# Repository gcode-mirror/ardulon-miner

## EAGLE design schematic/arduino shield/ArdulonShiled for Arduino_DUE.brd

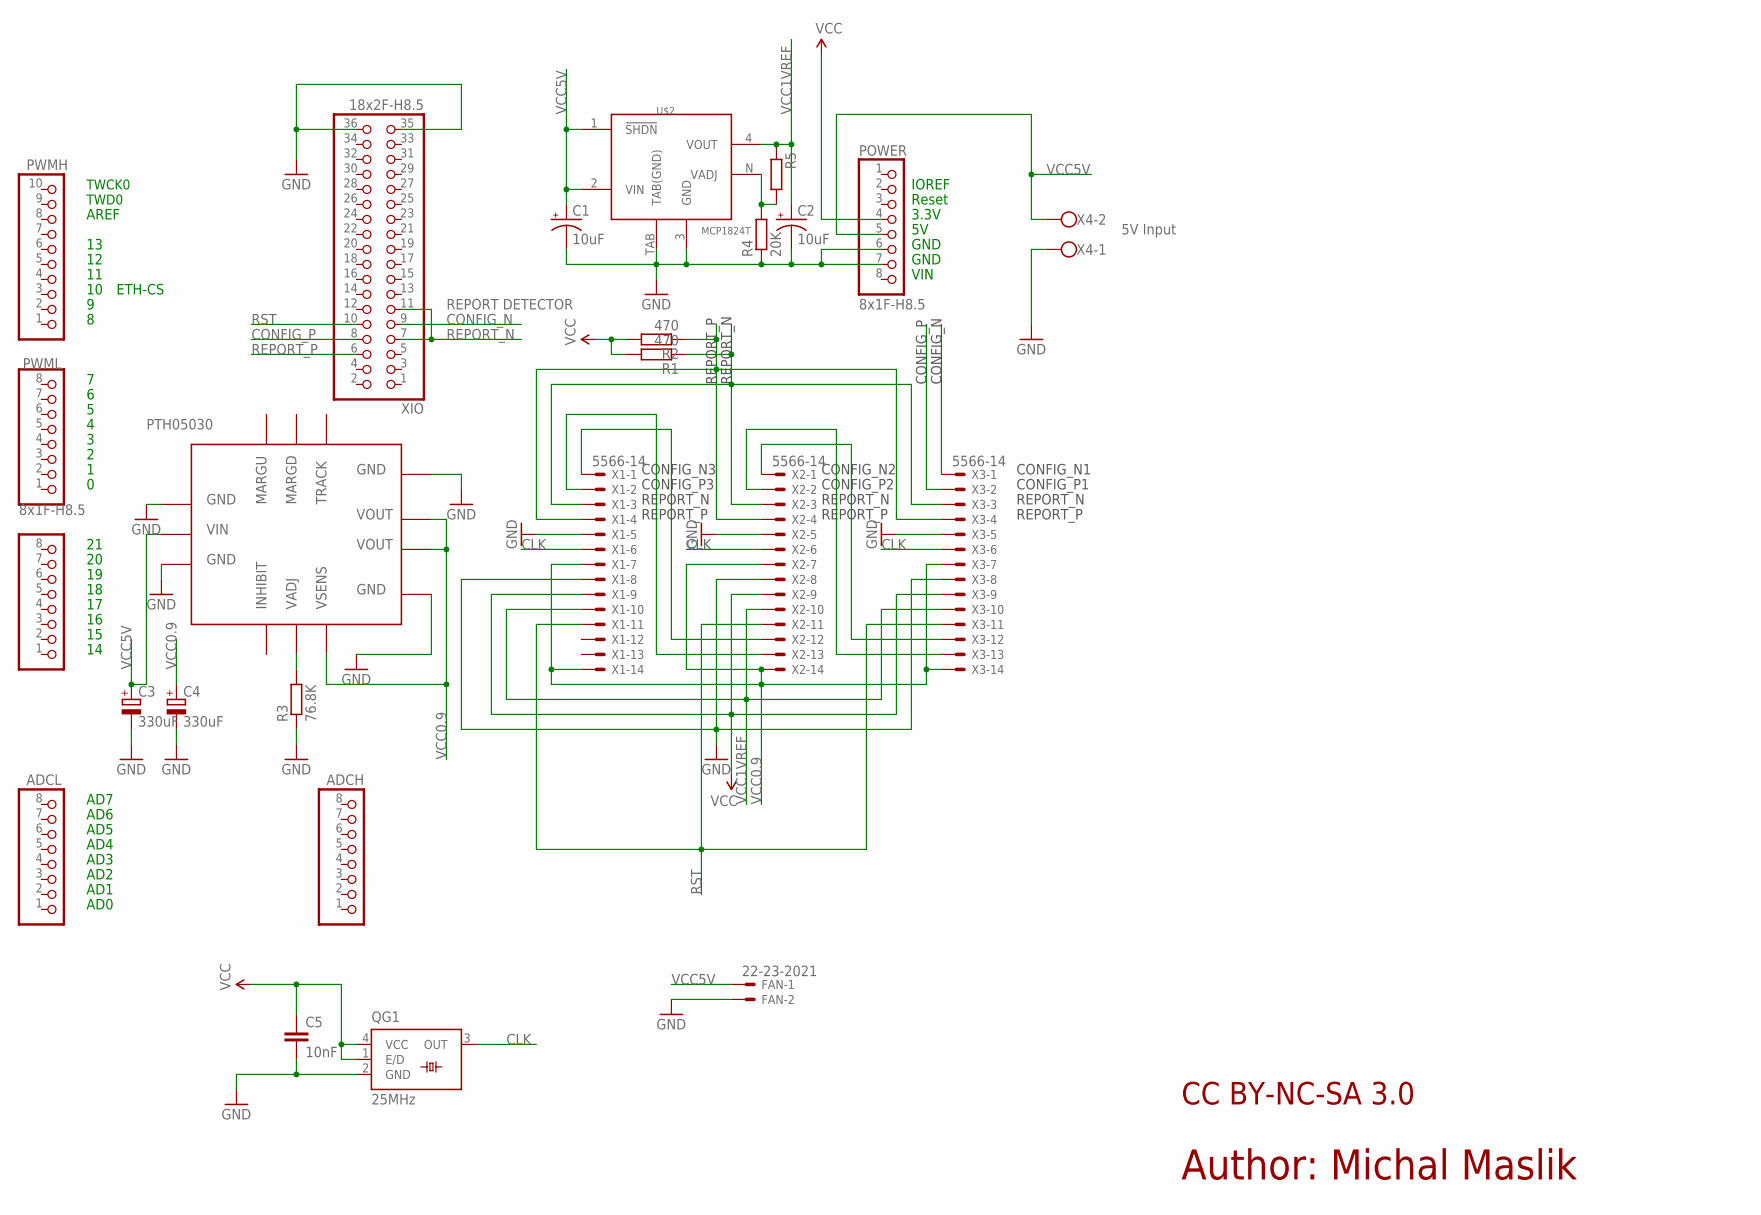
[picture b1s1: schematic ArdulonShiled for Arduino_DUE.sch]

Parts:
ADCH: 8x1F-H8.5; 1X08
ADCL: 8x1F-H8.5; 1X08
C1, C2: 10uF; EIA3528-KIT
C3, C4: 330uF; SMC_E
C5: 10nF; C0805
COMMUNICATION: 8x1F-H8.5; 1X08
FAN: 22-23-2021
POWER: 8x1F-H8.5; 1X08
PWMH: 10x1F-H8.5; 1X10
PWML: 8x1F-H8.5; 1X08
QG1: 25MHz; SM77H
R1, R2: 470; M0805
R3: 76.8K; M0805
R4: 20K; M0805
R5: R-EU_M0805; M0805
U$1: PTH05030
U$2: MCP1824T; SOT223-5
X1, X2, X3: 5566-14
X4: W237-102
XIO: 18x2F-H8.5; 2X18

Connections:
CLK: QG1.3 (OUT), X1.6, X2.6, X3.6
CONFIG_N: X3.1, XIO.9
CONFIG_P: X3.2, XIO.8
GND: C1.C (-), C2.C (-), C3.-, C4.-, C5.2, FAN.2, POWER.6, POWER.7, QG1.2 (GND), R3.1, R4.1, U$1.1, U$1.3, U$1.7, U$1.10, U$2.3 (GND), U$2.TAB (TAB(GND)), X1.5, X1.8, X2.5, X2.8, X3.5, X3.8, X4.1, XIO.35, XIO.36
unnamed: R4.2, R5.2, U$2.N (VADJ)
unnamed: X2.1, X3.12
unnamed: R3.2, U$1.5
unnamed: X2.2, X3.13
unnamed: X1.1, X2.12
unnamed: X1.2, X2.13
REPORT_N: R1.1, X1.3, X2.3, X3.3, XIO.7, XIO.11
REPORT_P: R2.1, X1.4, X2.4, X3.4, XIO.6
RST: X1.11, X2.11, X3.11, XIO.10
VCC: C5.1, POWER.4, QG1.1 (E/D), QG1.4 (VCC), R1.2, R2.2, X1.9, X2.9, X3.9
VCC0.9: C4.+, U$1.6, U$1.8, U$1.9, X1.7, X1.14, X2.7, X2.14, X3.7, X3.14
VCC1REF: C2.A (+), R5.1, U$2.4 (VOUT), X1.10, X2.10, X3.10
VCC5V: C1.A (+), C3.+, FAN.1, POWER.5, U$1.2, U$2.1 (!SHDN), U$2.2 (VIN), X4.2

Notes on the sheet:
IOREF
TWCK0
TWD0
AD1
AD2
AD3
AD4
AD5
AD6
AD0
AREF
AD7
ETH-CS
3.3V
GND
VIN
Reset
REPORT_P
REPORT_N
CONFIG_P
CONFIG_N
VCC1VREF
VCC0.9
5V Input
VCC5V
RST
CONFIG_N1
CONFIG_P1
CONFIG_N2
CONFIG_P2
CONFIG_P3
CONFIG_N3
CLK
Author: Michal Maslik
REPORT DETECTOR
CC BY-NC-SA 3.0

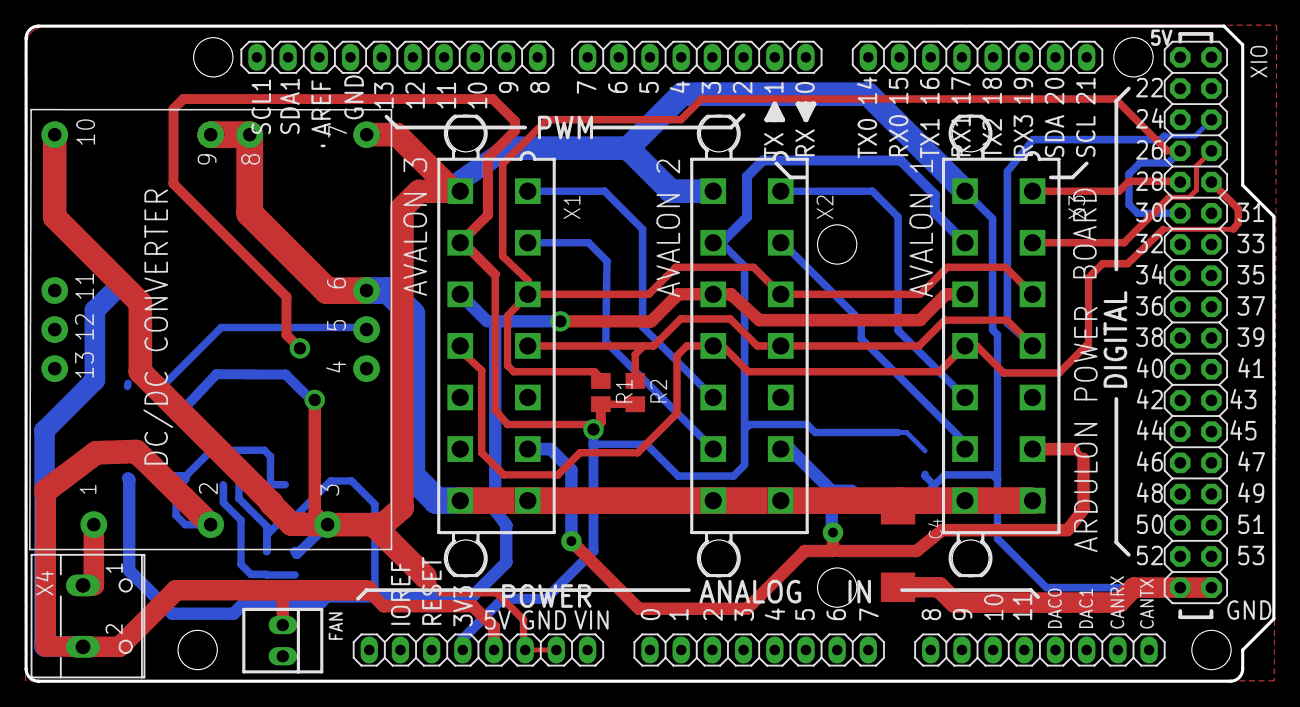
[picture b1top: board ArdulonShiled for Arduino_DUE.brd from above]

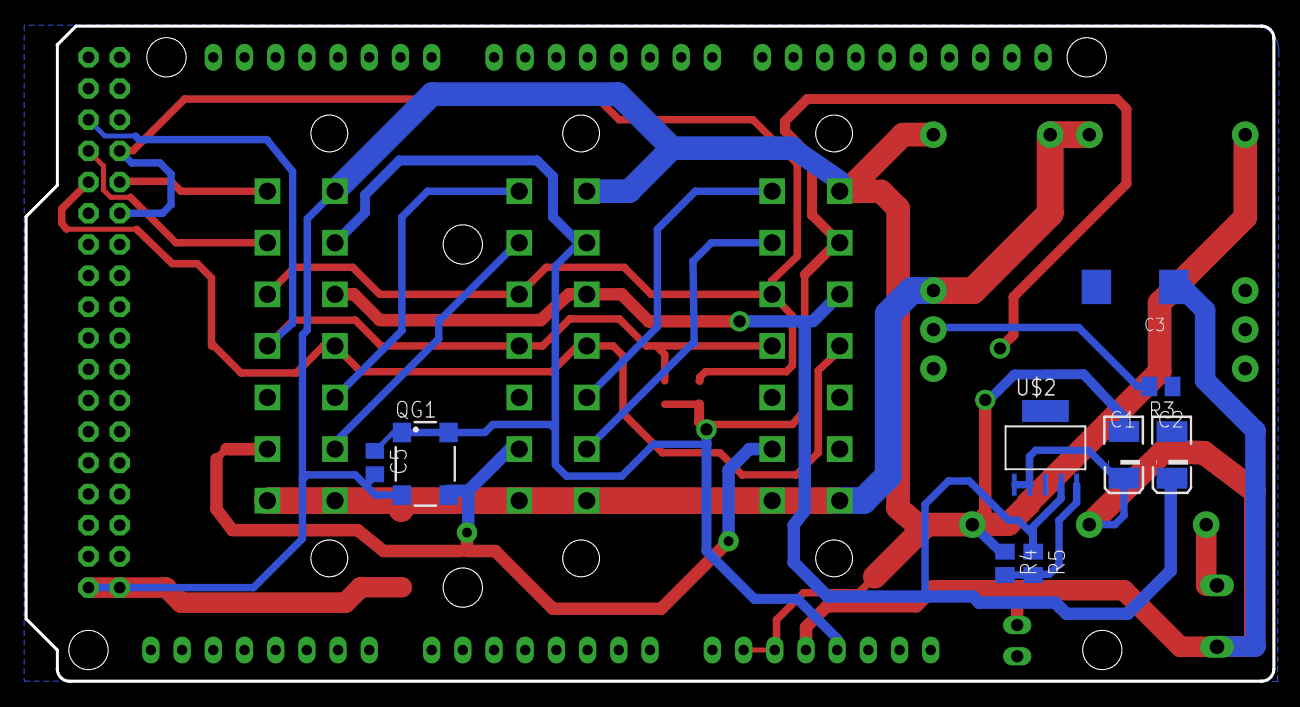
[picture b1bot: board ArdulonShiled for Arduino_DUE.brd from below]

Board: 4 copper layers, 101.6 x 53.3 mm, 25 parts (9 on the bottom side), 17 nets.

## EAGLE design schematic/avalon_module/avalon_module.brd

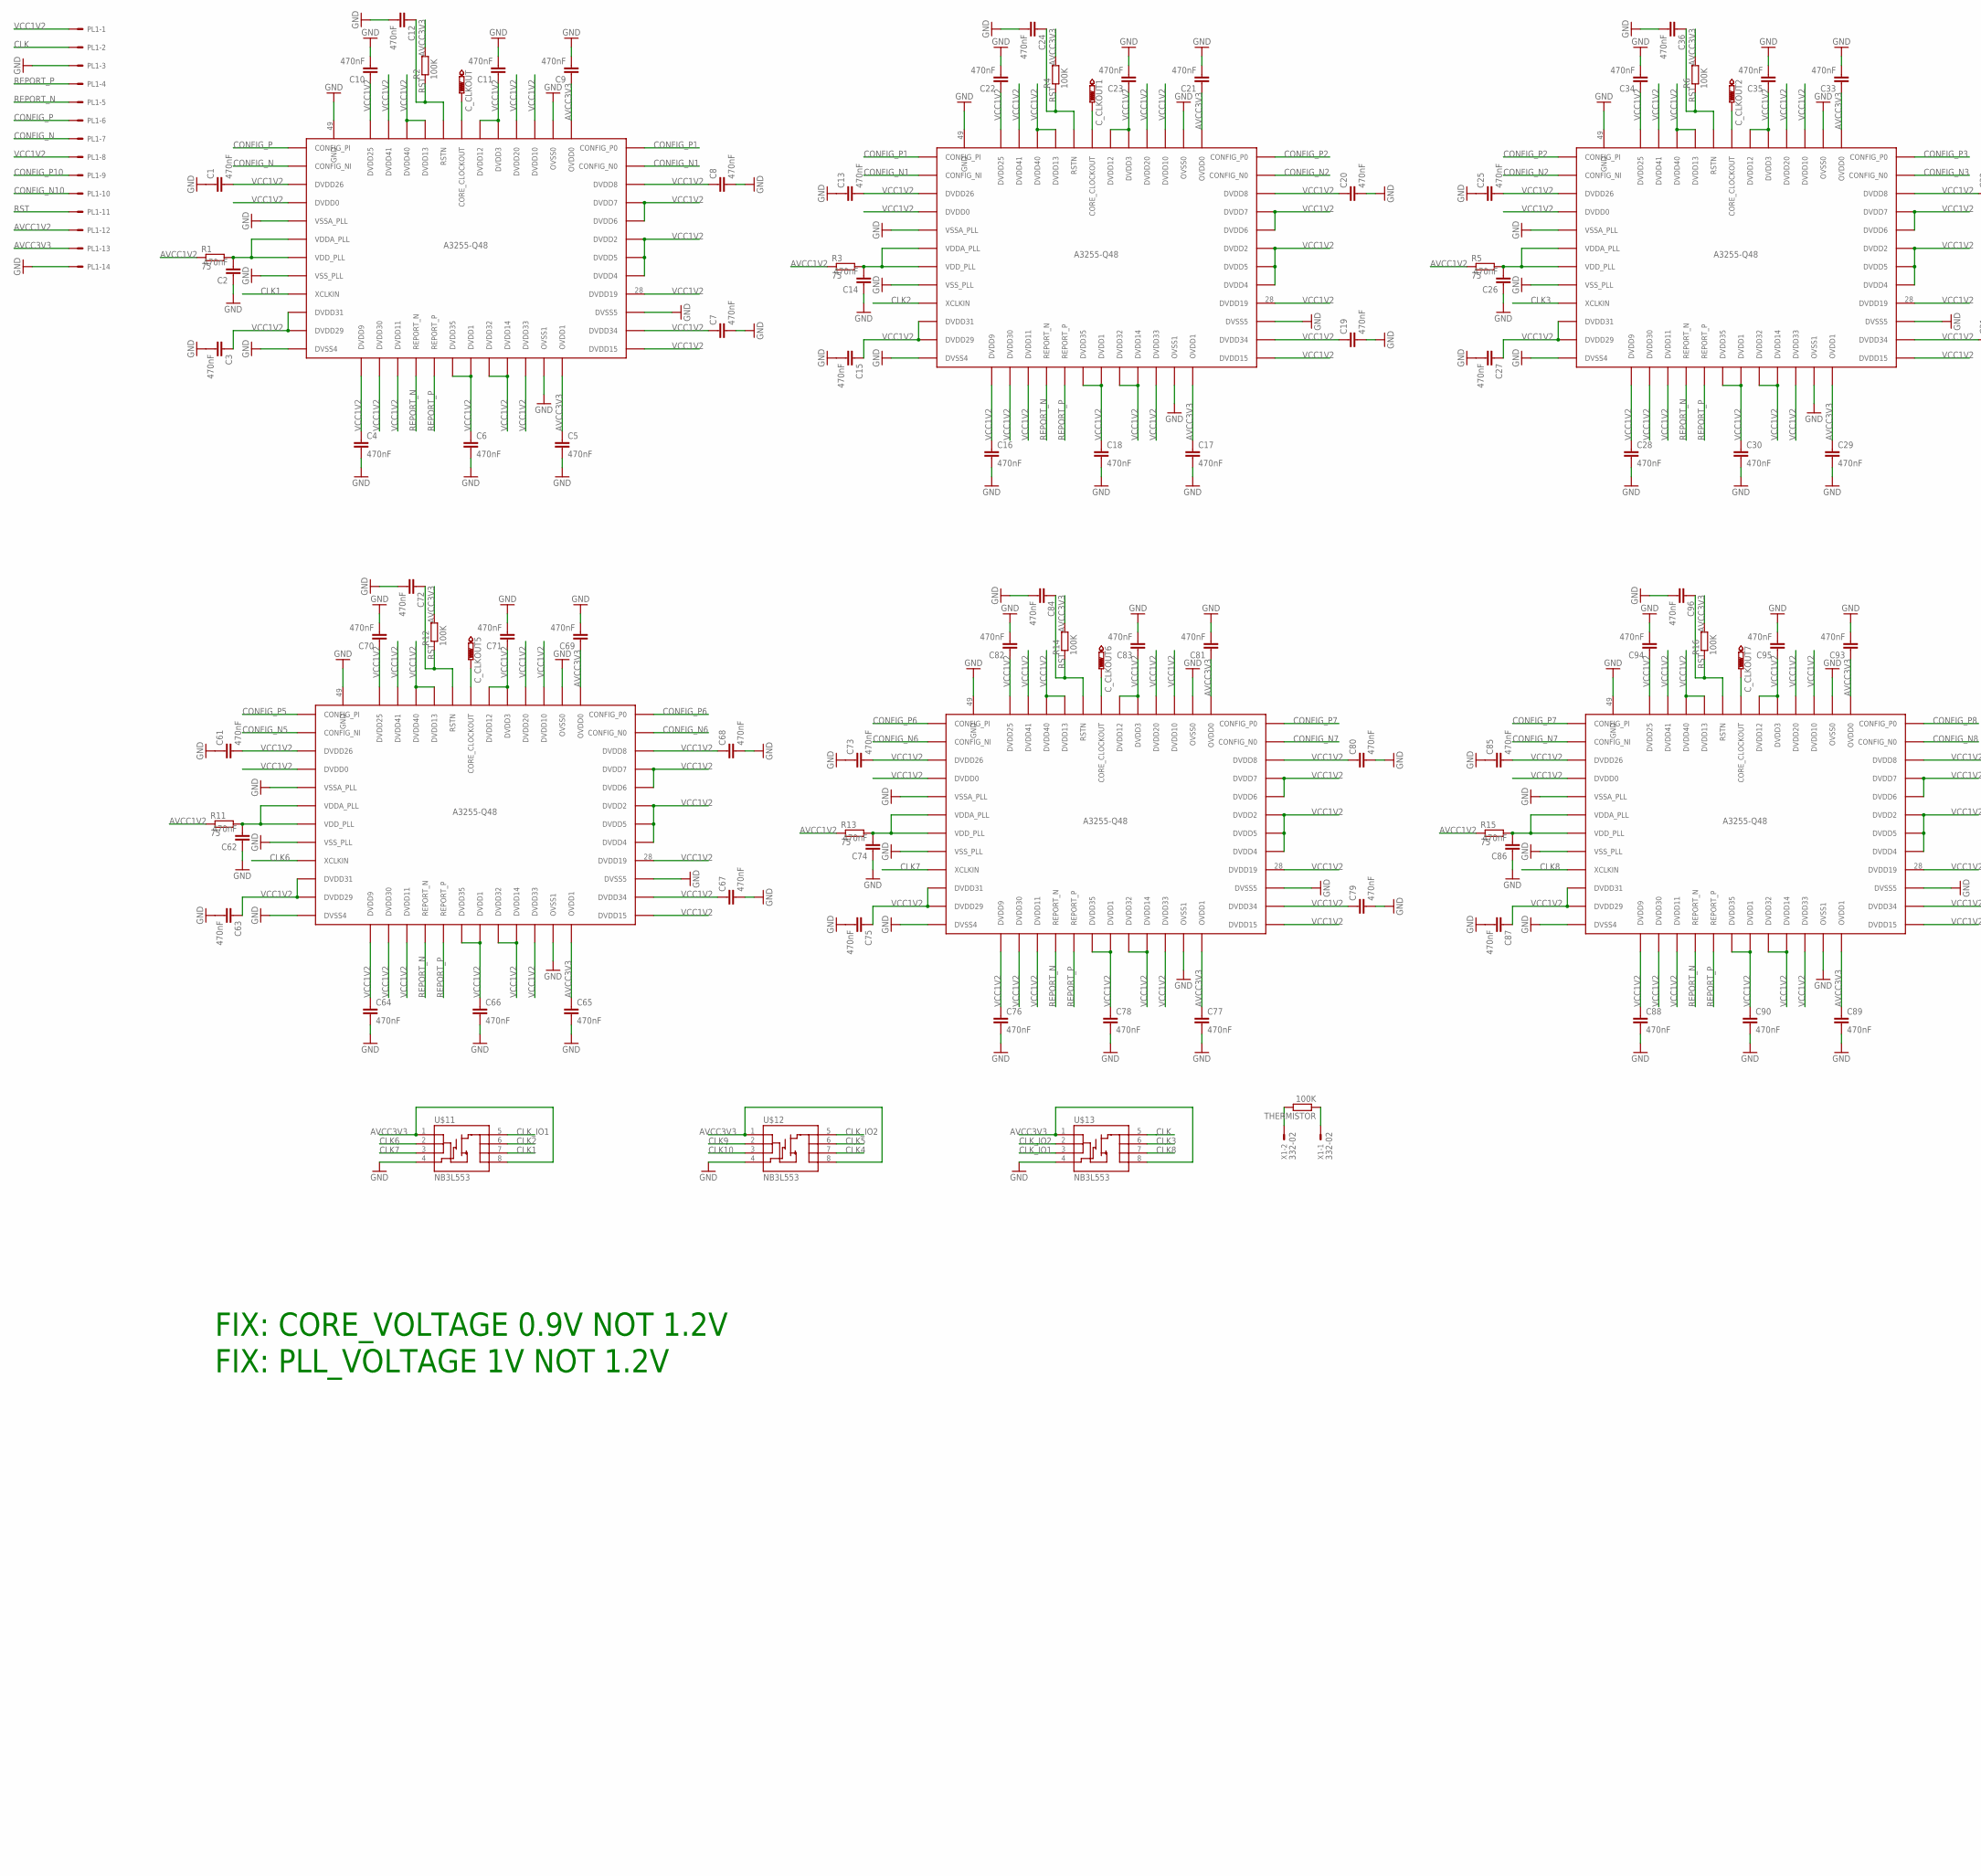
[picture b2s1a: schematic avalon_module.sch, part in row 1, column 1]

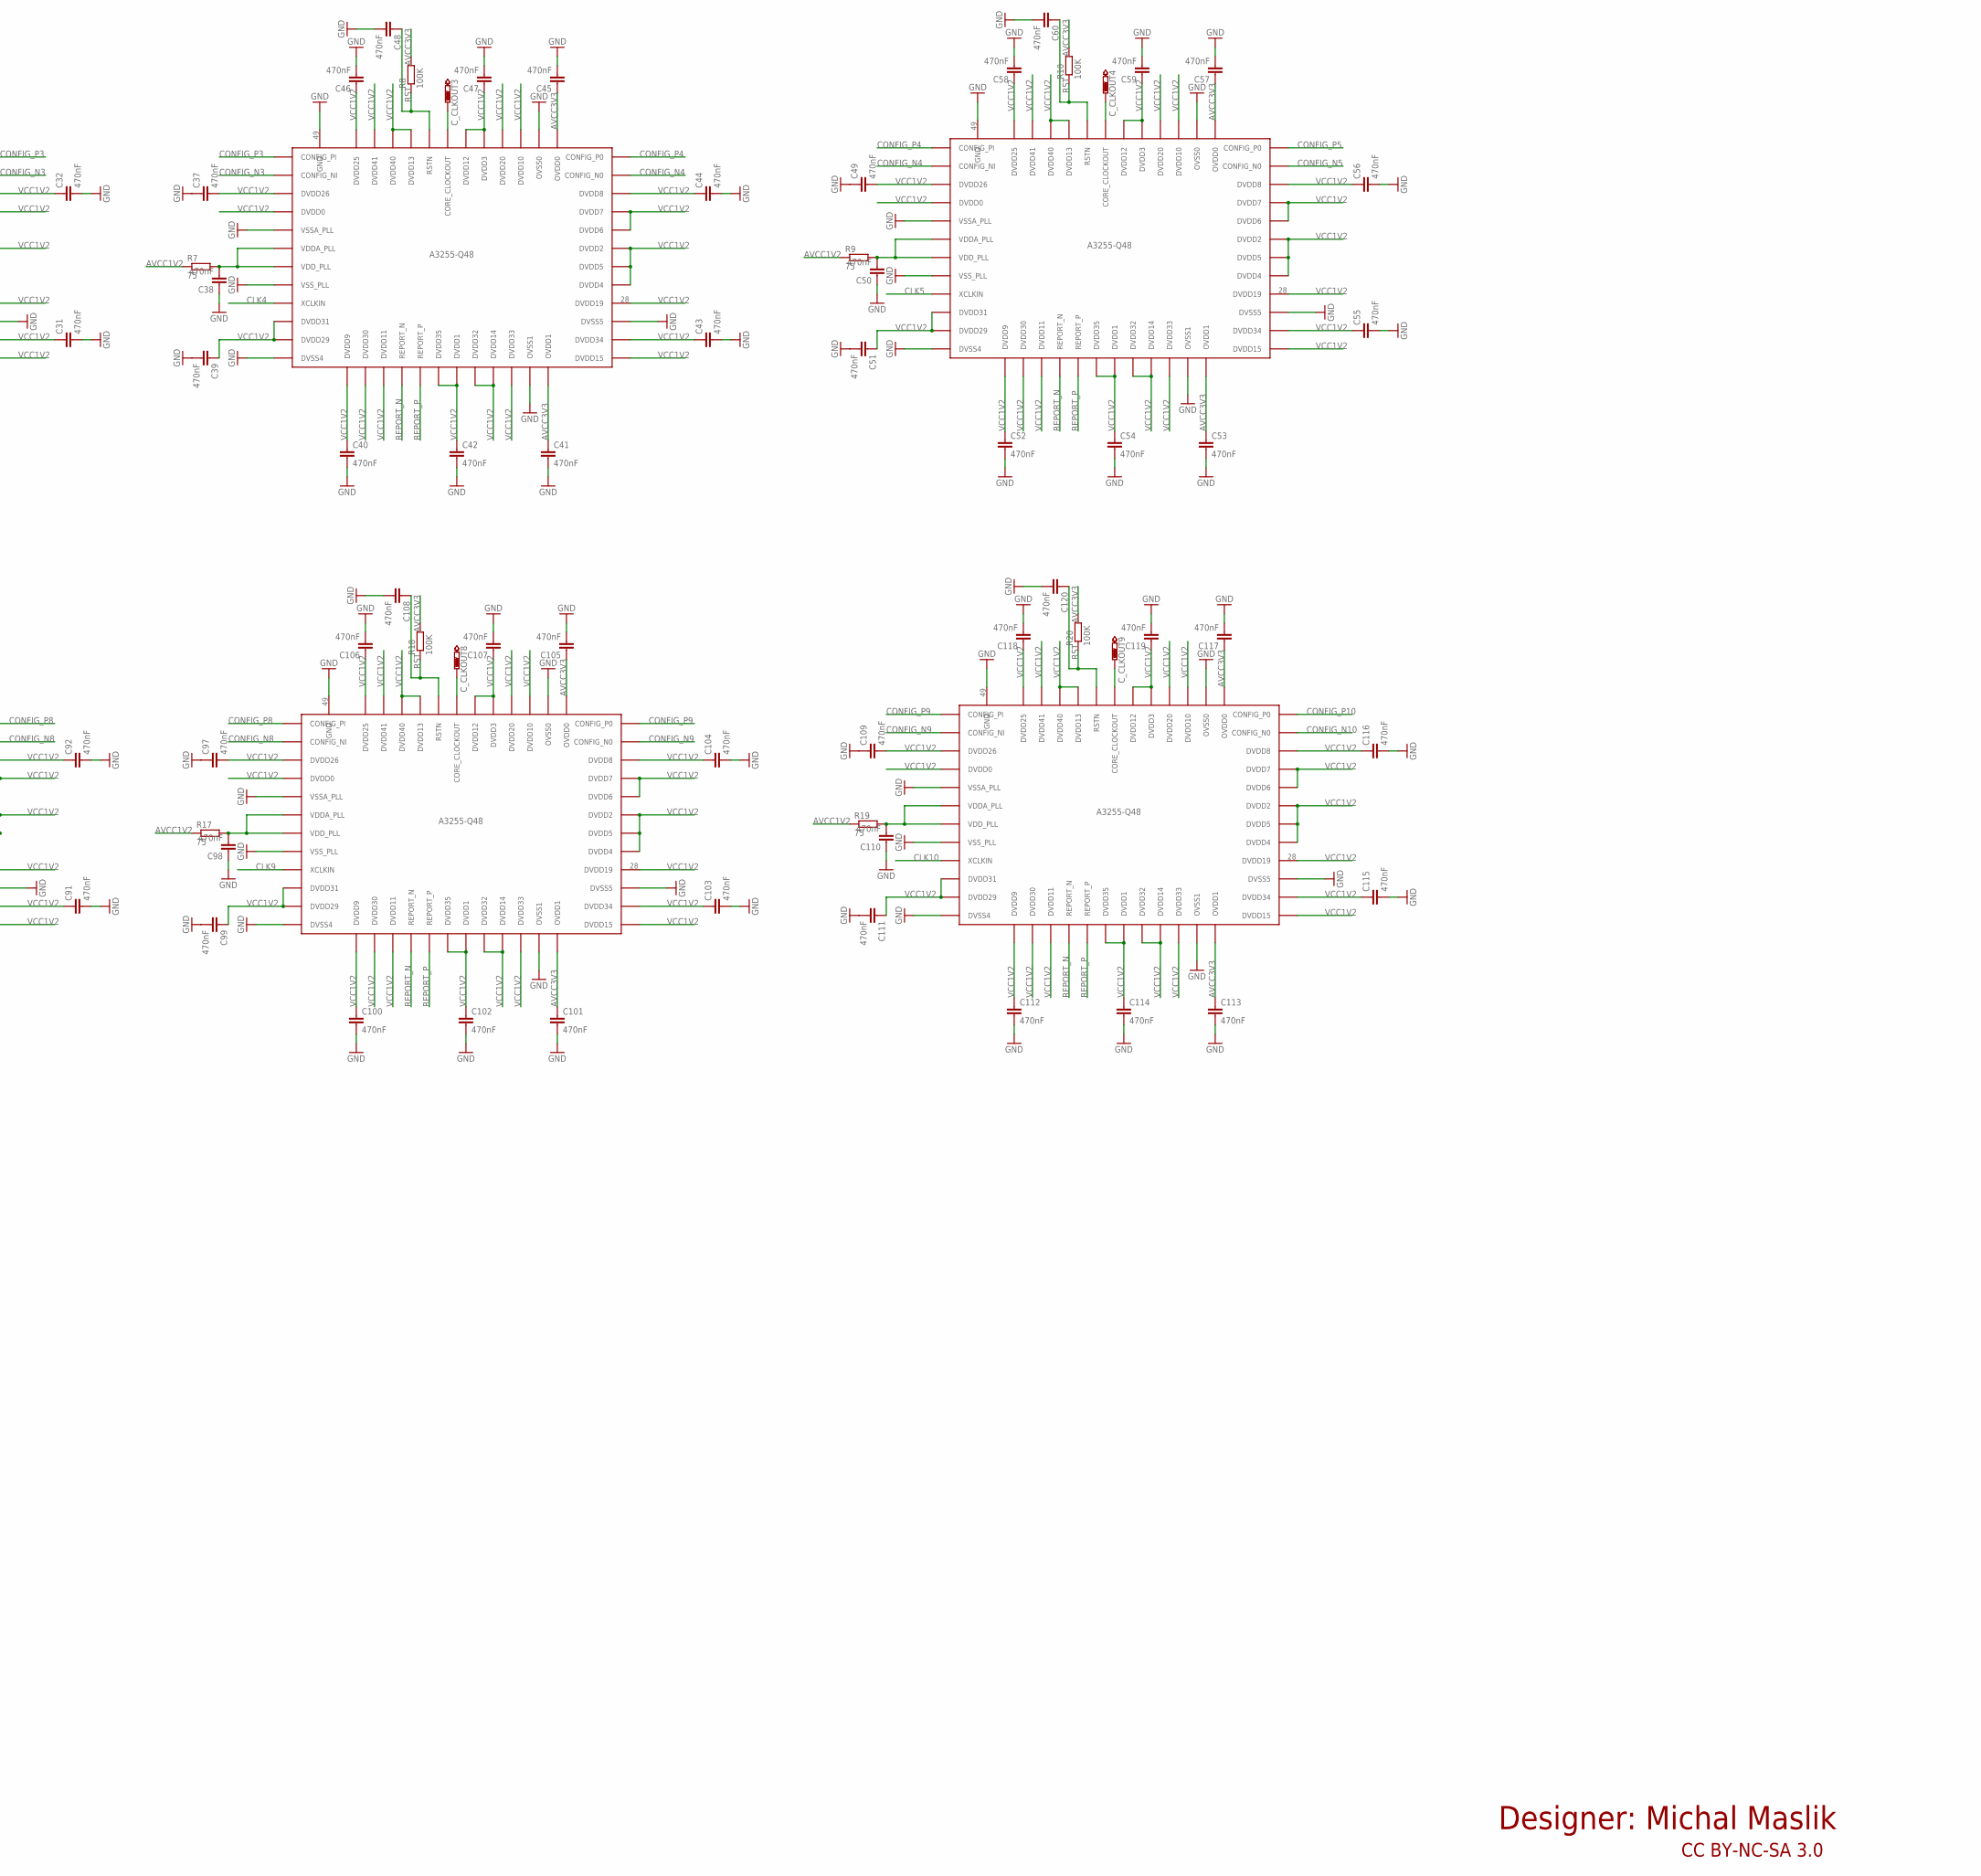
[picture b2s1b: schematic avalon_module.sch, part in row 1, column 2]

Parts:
C1, C2, C3, C4, C5, C6, C7, C8, C9, C10, C11, C12, C13, C14, C15, C16, C17, C18, C19, C20, C21, C22, C23, C24, C25, C26, C27, C28, C29, C30, C31, C32, C33, C34, C35, C36, C37, C38, C39, C40, C41, C42, C43, C44, C45, C46, C47, C48, C49, C50, C51, C52, C53, C54, C55, C56, C57, C58, C59, C60, C61, C62, C63, C64, C65, C66, C67, C68, C69, C70, C71, C72, C73, C74, C75, C76, C77, C78, C79, C80, C81, C82, C83, C84, C85, C86, C87, C88, C89, C90, C91, C92, C93, C94, C95, C96, C97, C98, C99, C100, C101, C102, C103, C104, C105, C106, C107, C108, C109, C110, C111, C112, C113, C114, C115, C116, C117, C118, C119, C120: 470nF; C0603K
C_CLKOUT, C_CLKOUT1, C_CLKOUT2, C_CLKOUT3, C_CLKOUT4, C_CLKOUT5, C_CLKOUT6, C_CLKOUT7, C_CLKOUT8, C_CLKOUT9: PTR1TP07R; TP07R
PL1: 555X-14H; 5569-14
R1, R3, R5, R7, R9, R11, R13, R15, R17, R19: 75; R0603
R2, R4, R6, R8, R10, R12, R14, R16, R18, R20: 100K; R0603
THERMISTOR: 100K; R0603
U$1, U$2, U$3, U$4, U$5, U$6, U$7, U$8, U$9, U$10: A3255Q48
U$11, U$12, U$13: NB3L553; SO08
X1: 332-02

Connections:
$1: C14.2, R3.2, U$2.6 (VDDA_PLL), U$2.7 (VDD_PLL)
$2: C26.2, R5.2, U$3.6 (VDDA_PLL), U$3.7 (VDD_PLL)
$3: C2.2, R1.2, U$1.6 (VDDA_PLL), U$1.7 (VDD_PLL)
$4: C38.2, R7.2, U$4.6 (VDDA_PLL), U$4.7 (VDD_PLL)
$5: C50.2, R9.2, U$5.6 (VDDA_PLL), U$5.7 (VDD_PLL)
$6: C62.2, R11.2, U$6.6 (VDDA_PLL), U$6.7 (VDD_PLL)
$7: C74.2, R13.2, U$7.6 (VDDA_PLL), U$7.7 (VDD_PLL)
$8: C86.2, R15.2, U$8.6 (VDDA_PLL), U$8.7 (VDD_PLL)
$9: C98.2, R17.2, U$9.6 (VDDA_PLL), U$9.7 (VDD_PLL)
$10: C110.2, R19.2, U$10.6 (VDDA_PLL), U$10.7 (VDD_PLL)
AVCC1V2: PL1.12, R1.1, R3.1, R5.1, R7.1, R9.1, R11.1, R13.1, R15.1, R17.1, R19.1
AVCC3V3: C5.1, C9.1, C17.1, C21.1, C29.1, C33.1, C41.1, C45.1, C53.1, C57.1, C65.1, C69.1, C77.1, C81.1, C89.1, C93.1, C101.1, C105.1, C113.1, C117.1, PL1.13, R2.2, R4.2, R6.2, R8.2, R10.2, R12.2, R14.2, R16.2, R18.2, R20.2, U$1.24 (OVDD1), U$1.37 (OVDD0), U$2.24 (OVDD1), U$2.37 (OVDD0), U$3.24 (OVDD1), U$3.37 (OVDD0), U$4.24 (OVDD1), U$4.37 (OVDD0), U$5.24 (OVDD1), U$5.37 (OVDD0), U$6.24 (OVDD1), U$6.37 (OVDD0), U$7.24 (OVDD1), U$7.37 (OVDD0), U$8.24 (OVDD1), U$8.37 (OVDD0), U$9.24 (OVDD1), U$9.37 (OVDD0), U$10.24 (OVDD1), U$10.37 (OVDD0), U$11.1 (S), U$11.8 (D), U$12.1 (S), U$12.8 (D), U$13.1 (S), U$13.8 (D)
CLK: PL1.2, U$13.5 (D)
CLK1: U$1.9 (XCLKIN), U$11.7 (D)
CLK2: U$2.9 (XCLKIN), U$11.6 (D)
CLK3: U$3.9 (XCLKIN), U$13.6 (D)
CLK4: U$4.9 (XCLKIN), U$12.7 (D)
CLK5: U$5.9 (XCLKIN), U$12.6 (D)
CLK6: U$6.9 (XCLKIN), U$11.2 (S)
CLK7: U$7.9 (XCLKIN), U$11.3 (S)
CLK8: U$8.9 (XCLKIN), U$13.7 (D)
CLK9: U$9.9 (XCLKIN), U$12.2 (S)
CLK10: U$10.9 (XCLKIN), U$12.3 (S)
CLK_IO1: U$11.5 (D), U$13.3 (S)
CLK_IO2: U$12.5 (D), U$13.2 (S)
CONFIG_N: PL1.7, U$1.2 (CONFIG_NI)
CONFIG_N1: U$1.35 (CONFIG_N0), U$2.2 (CONFIG_NI)
CONFIG_N2: U$2.35 (CONFIG_N0), U$3.2 (CONFIG_NI)
CONFIG_N3: U$3.35 (CONFIG_N0), U$4.2 (CONFIG_NI)
CONFIG_N4: U$4.35 (CONFIG_N0), U$5.2 (CONFIG_NI)
CONFIG_N5: U$5.35 (CONFIG_N0), U$6.2 (CONFIG_NI)
CONFIG_N6: U$6.35 (CONFIG_N0), U$7.2 (CONFIG_NI)
CONFIG_N7: U$7.35 (CONFIG_N0), U$8.2 (CONFIG_NI)
CONFIG_N8: U$8.35 (CONFIG_N0), U$9.2 (CONFIG_NI)
CONFIG_N9: U$9.35 (CONFIG_N0), U$10.2 (CONFIG_NI)
CONFIG_N10: PL1.10, U$10.35 (CONFIG_N0)
CONFIG_P: PL1.6, U$1.1 (CONFIG_PI)
CONFIG_P1: U$1.36 (CONFIG_P0), U$2.1 (CONFIG_PI)
CONFIG_P2: U$2.36 (CONFIG_P0), U$3.1 (CONFIG_PI)
CONFIG_P3: U$3.36 (CONFIG_P0), U$4.1 (CONFIG_PI)
CONFIG_P4: U$4.36 (CONFIG_P0), U$5.1 (CONFIG_PI)
CONFIG_P5: U$5.36 (CONFIG_P0), U$6.1 (CONFIG_PI)
CONFIG_P6: U$6.36 (CONFIG_P0), U$7.1 (CONFIG_PI)
CONFIG_P7: U$7.36 (CONFIG_P0), U$8.1 (CONFIG_PI)
CONFIG_P8: U$8.36 (CONFIG_P0), U$9.1 (CONFIG_PI)
CONFIG_P9: U$9.36 (CONFIG_P0), U$10.1 (CONFIG_PI)
CONFIG_P10: PL1.9, U$10.36 (CONFIG_P0)
GND: C1.1, C2.1, C3.2, C4.2, C5.2, C6.2, C7.2, C8.2, C9.2, C10.2, C11.2, C12.2, C13.1, C14.1, C15.2, C16.2, C17.2, C18.2, C19.2, C20.2, C21.2, C22.2, C23.2, C24.2, C25.1, C26.1, C27.2, C28.2, C29.2, C30.2, C31.2, C32.2, C33.2, C34.2, C35.2, C36.2, C37.1, C38.1, C39.2, C40.2, C41.2, C42.2, C43.2, C44.2, C45.2, C46.2, C47.2, C48.2, C49.1, C50.1, C51.2, C52.2, C53.2, C54.2, C55.2, C56.2, C57.2, C58.2, C59.2, C60.2, C61.1, C62.1, C63.2, C64.2, C65.2, C66.2, C67.2, C68.2, C69.2, C70.2, C71.2, C72.2, C73.1, C74.1, C75.2, C76.2, C77.2, C78.2, C79.2, C80.2, C81.2, C82.2, C83.2, C84.2, C85.1, C86.1, C87.2, C88.2, C89.2, C90.2, C91.2, C92.2, C93.2, C94.2, C95.2, C96.2, C97.1, C98.1, C99.2, C100.2, C101.2, C102.2, C103.2, C104.2, C105.2, C106.2, C107.2, C108.2, C109.1, C110.1, C111.2, C112.2, C113.2, C114.2, C115.2, C116.2, C117.2, C118.2, C119.2, C120.2, PL1.3, PL1.14, U$1.5 (VSSA_PLL), U$1.8 (VSS_PLL), U$1.12 (DVSS4), U$1.23 (OVSS1), U$1.27 (DVSS5), U$1.38 (OVSS0), U$1.49 (GND), U$2.5 (VSSA_PLL), U$2.8 (VSS_PLL), U$2.12 (DVSS4), U$2.23 (OVSS1), U$2.27 (DVSS5), U$2.38 (OVSS0), U$2.49 (GND), U$3.5 (VSSA_PLL), U$3.8 (VSS_PLL), U$3.12 (DVSS4), U$3.23 (OVSS1), U$3.27 (DVSS5), U$3.38 (OVSS0), U$3.49 (GND), U$4.5 (VSSA_PLL), U$4.8 (VSS_PLL), U$4.12 (DVSS4), U$4.23 (OVSS1), U$4.27 (DVSS5), U$4.38 (OVSS0), U$4.49 (GND), U$5.5 (VSSA_PLL), U$5.8 (VSS_PLL), U$5.12 (DVSS4), U$5.23 (OVSS1), U$5.27 (DVSS5), U$5.38 (OVSS0), U$5.49 (GND), U$6.5 (VSSA_PLL), U$6.8 (VSS_PLL), U$6.12 (DVSS4), U$6.23 (OVSS1), U$6.27 (DVSS5), U$6.38 (OVSS0), U$6.49 (GND), U$7.5 (VSSA_PLL), U$7.8 (VSS_PLL), U$7.12 (DVSS4), U$7.23 (OVSS1), U$7.27 (DVSS5), U$7.38 (OVSS0), U$7.49 (GND), U$8.5 (VSSA_PLL), U$8.8 (VSS_PLL), U$8.12 (DVSS4), U$8.23 (OVSS1), U$8.27 (DVSS5), U$8.38 (OVSS0), U$8.49 (GND), U$9.5 (VSSA_PLL), U$9.8 (VSS_PLL), U$9.12 (DVSS4), U$9.23 (OVSS1), U$9.27 (DVSS5), U$9.38 (OVSS0), U$9.49 (GND), U$10.5 (VSSA_PLL), U$10.8 (VSS_PLL), U$10.12 (DVSS4), U$10.23 (OVSS1), U$10.27 (DVSS5), U$10.38 (OVSS0), U$10.49 (GND), U$11.4 (G), U$12.4 (G), U$13.4 (G)
unnamed: C_CLKOUT.TP, U$1.43 (CORE_CLOCKOUT)
unnamed: C_CLKOUT5.TP, U$6.43 (CORE_CLOCKOUT)
unnamed: C_CLKOUT1.TP, U$2.43 (CORE_CLOCKOUT)
unnamed: C_CLKOUT2.TP, U$3.43 (CORE_CLOCKOUT)
unnamed: C_CLKOUT3.TP, U$4.43 (CORE_CLOCKOUT)
unnamed: C_CLKOUT4.TP, U$5.43 (CORE_CLOCKOUT)
unnamed: C_CLKOUT9.TP, U$10.43 (CORE_CLOCKOUT)
unnamed: C_CLKOUT8.TP, U$9.43 (CORE_CLOCKOUT)
unnamed: C_CLKOUT7.TP, U$8.43 (CORE_CLOCKOUT)
unnamed: C_CLKOUT6.TP, U$7.43 (CORE_CLOCKOUT)
unnamed: THERMISTOR.2, X1.2
unnamed: THERMISTOR.1, X1.1
REPORT_N: PL1.5, U$1.16 (REPORT_N), U$2.16 (REPORT_N), U$3.16 (REPORT_N), U$4.16 (REPORT_N), U$5.16 (REPORT_N), U$6.16 (REPORT_N), U$7.16 (REPORT_N), U$8.16 (REPORT_N), U$9.16 (REPORT_N), U$10.16 (REPORT_N)
REPORT_P: PL1.4, U$1.17 (REPORT_P), U$2.17 (REPORT_P), U$3.17 (REPORT_P), U$4.17 (REPORT_P), U$5.17 (REPORT_P), U$6.17 (REPORT_P), U$7.17 (REPORT_P), U$8.17 (REPORT_P), U$9.17 (REPORT_P), U$10.17 (REPORT_P)
RST: C12.1, C24.1, C36.1, C48.1, C60.1, C72.1, C84.1, C96.1, C108.1, C120.1, PL1.11, R2.1, R4.1, R6.1, R8.1, R10.1, R12.1, R14.1, R16.1, R18.1, R20.1, U$1.44 (RSTN), U$2.44 (RSTN), U$3.44 (RSTN), U$4.44 (RSTN), U$5.44 (RSTN), U$6.44 (RSTN), U$7.44 (RSTN), U$8.44 (RSTN), U$9.44 (RSTN), U$10.44 (RSTN)
VCC1V2: C1.2, C3.1, C4.1, C6.1, C7.1, C8.1, C10.1, C11.1, C13.2, C15.1, C16.1, C18.1, C19.1, C20.1, C22.1, C23.1, C25.2, C27.1, C28.1, C30.1, C31.1, C32.1, C34.1, C35.1, C37.2, C39.1, C40.1, C42.1, C43.1, C44.1, C46.1, C47.1, C49.2, C51.1, C52.1, C54.1, C55.1, C56.1, C58.1, C59.1, C61.2, C63.1, C64.1, C66.1, C67.1, C68.1, C70.1, C71.1, C73.2, C75.1, C76.1, C78.1, C79.1, C80.1, C82.1, C83.1, C85.2, C87.1, C88.1, C90.1, C91.1, C92.1, C94.1, C95.1, C97.2, C99.1, C100.1, C102.1, C103.1, C104.1, C106.1, C107.1, C109.2, C111.1, C112.1, C114.1, C115.1, C116.1, C118.1, C119.1, PL1.1, PL1.8, U$1.3 (DVDD26), U$1.4 (DVDD0), U$1.10 (DVDD31), U$1.11 (DVDD29), U$1.13 (DVDD9), U$1.14 (DVDD30), U$1.15 (DVDD11), U$1.18 (DVDD35), U$1.19 (DVDD1), U$1.20 (DVDD32), U$1.21 (DVDD14), U$1.22 (DVDD33), U$1.25 (DVDD15), U$1.26 (DVDD34), U$1.28 (DVDD19), U$1.29 (DVDD4), U$1.30 (DVDD5), U$1.31 (DVDD2), U$1.32 (DVDD6), U$1.33 (DVDD7), U$1.34 (DVDD8), U$1.39 (DVDD10), U$1.40 (DVDD20), U$1.41 (DVDD3), U$1.42 (DVDD12), U$1.45 (DVDD13), U$1.46 (DVDD40), U$1.47 (DVDD41), U$1.48 (DVDD25), U$2.3 (DVDD26), U$2.4 (DVDD0), U$2.10 (DVDD31), U$2.11 (DVDD29), U$2.13 (DVDD9), U$2.14 (DVDD30), U$2.15 (DVDD11), U$2.18 (DVDD35), U$2.19 (DVDD1), U$2.20 (DVDD32), U$2.21 (DVDD14), U$2.22 (DVDD33), U$2.25 (DVDD15), U$2.26 (DVDD34), U$2.28 (DVDD19), U$2.29 (DVDD4), U$2.30 (DVDD5), U$2.31 (DVDD2), U$2.32 (DVDD6), U$2.33 (DVDD7), U$2.34 (DVDD8), U$2.39 (DVDD10), U$2.40 (DVDD20), U$2.41 (DVDD3), U$2.42 (DVDD12), U$2.45 (DVDD13), U$2.46 (DVDD40), U$2.47 (DVDD41), U$2.48 (DVDD25), U$3.3 (DVDD26), U$3.4 (DVDD0), U$3.10 (DVDD31), U$3.11 (DVDD29), U$3.13 (DVDD9), U$3.14 (DVDD30), U$3.15 (DVDD11), U$3.18 (DVDD35), U$3.19 (DVDD1), U$3.20 (DVDD32), U$3.21 (DVDD14), U$3.22 (DVDD33), U$3.25 (DVDD15), U$3.26 (DVDD34), U$3.28 (DVDD19), U$3.29 (DVDD4), U$3.30 (DVDD5), U$3.31 (DVDD2), U$3.32 (DVDD6), U$3.33 (DVDD7), U$3.34 (DVDD8), U$3.39 (DVDD10), U$3.40 (DVDD20), U$3.41 (DVDD3), U$3.42 (DVDD12), U$3.45 (DVDD13), U$3.46 (DVDD40), U$3.47 (DVDD41), U$3.48 (DVDD25), U$4.3 (DVDD26), U$4.4 (DVDD0), U$4.10 (DVDD31), U$4.11 (DVDD29), U$4.13 (DVDD9), U$4.14 (DVDD30), U$4.15 (DVDD11), U$4.18 (DVDD35), U$4.19 (DVDD1), U$4.20 (DVDD32), U$4.21 (DVDD14), U$4.22 (DVDD33), U$4.25 (DVDD15), U$4.26 (DVDD34), U$4.28 (DVDD19), U$4.29 (DVDD4), U$4.30 (DVDD5), U$4.31 (DVDD2), U$4.32 (DVDD6), U$4.33 (DVDD7), U$4.34 (DVDD8), U$4.39 (DVDD10), U$4.40 (DVDD20), U$4.41 (DVDD3), U$4.42 (DVDD12), U$4.45 (DVDD13), U$4.46 (DVDD40), U$4.47 (DVDD41), U$4.48 (DVDD25), U$5.3 (DVDD26), U$5.4 (DVDD0), U$5.10 (DVDD31), U$5.11 (DVDD29), U$5.13 (DVDD9), U$5.14 (DVDD30), U$5.15 (DVDD11), U$5.18 (DVDD35), U$5.19 (DVDD1), U$5.20 (DVDD32), U$5.21 (DVDD14), U$5.22 (DVDD33), U$5.25 (DVDD15), U$5.26 (DVDD34), U$5.28 (DVDD19), U$5.29 (DVDD4), U$5.30 (DVDD5), U$5.31 (DVDD2), U$5.32 (DVDD6), U$5.33 (DVDD7), U$5.34 (DVDD8), U$5.39 (DVDD10), U$5.40 (DVDD20), U$5.41 (DVDD3), U$5.42 (DVDD12), U$5.45 (DVDD13), U$5.46 (DVDD40), U$5.47 (DVDD41), U$5.48 (DVDD25), U$6.3 (DVDD26), U$6.4 (DVDD0), U$6.10 (DVDD31), U$6.11 (DVDD29), U$6.13 (DVDD9), U$6.14 (DVDD30), U$6.15 (DVDD11), U$6.18 (DVDD35), U$6.19 (DVDD1), U$6.20 (DVDD32), U$6.21 (DVDD14), U$6.22 (DVDD33), U$6.25 (DVDD15), U$6.26 (DVDD34), U$6.28 (DVDD19), U$6.29 (DVDD4), U$6.30 (DVDD5), U$6.31 (DVDD2), U$6.32 (DVDD6), U$6.33 (DVDD7), U$6.34 (DVDD8), U$6.39 (DVDD10), U$6.40 (DVDD20), U$6.41 (DVDD3), U$6.42 (DVDD12), U$6.45 (DVDD13), U$6.46 (DVDD40), U$6.47 (DVDD41), U$6.48 (DVDD25), U$7.3 (DVDD26), U$7.4 (DVDD0), U$7.10 (DVDD31), U$7.11 (DVDD29), U$7.13 (DVDD9), U$7.14 (DVDD30), U$7.15 (DVDD11), U$7.18 (DVDD35), U$7.19 (DVDD1), U$7.20 (DVDD32), U$7.21 (DVDD14), U$7.22 (DVDD33), U$7.25 (DVDD15), U$7.26 (DVDD34), U$7.28 (DVDD19), U$7.29 (DVDD4), U$7.30 (DVDD5), U$7.31 (DVDD2), U$7.32 (DVDD6), U$7.33 (DVDD7), U$7.34 (DVDD8), U$7.39 (DVDD10), U$7.40 (DVDD20), U$7.41 (DVDD3), U$7.42 (DVDD12), U$7.45 (DVDD13), U$7.46 (DVDD40), U$7.47 (DVDD41), U$7.48 (DVDD25), U$8.3 (DVDD26), U$8.4 (DVDD0), U$8.10 (DVDD31), U$8.11 (DVDD29), U$8.13 (DVDD9), U$8.14 (DVDD30), U$8.15 (DVDD11), U$8.18 (DVDD35), U$8.19 (DVDD1), U$8.20 (DVDD32), U$8.21 (DVDD14), U$8.22 (DVDD33), U$8.25 (DVDD15), U$8.26 (DVDD34), U$8.28 (DVDD19), U$8.29 (DVDD4), U$8.30 (DVDD5), U$8.31 (DVDD2), U$8.32 (DVDD6), U$8.33 (DVDD7), U$8.34 (DVDD8), U$8.39 (DVDD10), U$8.40 (DVDD20), U$8.41 (DVDD3), U$8.42 (DVDD12), U$8.45 (DVDD13), U$8.46 (DVDD40), U$8.47 (DVDD41), U$8.48 (DVDD25), U$9.3 (DVDD26), U$9.4 (DVDD0), U$9.10 (DVDD31), U$9.11 (DVDD29), U$9.13 (DVDD9), U$9.14 (DVDD30), U$9.15 (DVDD11), U$9.18 (DVDD35), U$9.19 (DVDD1), U$9.20 (DVDD32), U$9.21 (DVDD14), U$9.22 (DVDD33), U$9.25 (DVDD15), U$9.26 (DVDD34), U$9.28 (DVDD19), U$9.29 (DVDD4), U$9.30 (DVDD5), U$9.31 (DVDD2), U$9.32 (DVDD6), U$9.33 (DVDD7), U$9.34 (DVDD8), U$9.39 (DVDD10), U$9.40 (DVDD20), U$9.41 (DVDD3), U$9.42 (DVDD12), U$9.45 (DVDD13), U$9.46 (DVDD40), U$9.47 (DVDD41), U$9.48 (DVDD25), U$10.3 (DVDD26), U$10.4 (DVDD0), U$10.10 (DVDD31), U$10.11 (DVDD29), U$10.13 (DVDD9), U$10.14 (DVDD30), U$10.15 (DVDD11), U$10.18 (DVDD35), U$10.19 (DVDD1), U$10.20 (DVDD32), U$10.21 (DVDD14), U$10.22 (DVDD33), U$10.25 (DVDD15), U$10.26 (DVDD34), U$10.28 (DVDD19), U$10.29 (DVDD4), U$10.30 (DVDD5), U$10.31 (DVDD2), U$10.32 (DVDD6), U$10.33 (DVDD7), U$10.34 (DVDD8), U$10.39 (DVDD10), U$10.40 (DVDD20), U$10.41 (DVDD3), U$10.42 (DVDD12), U$10.45 (DVDD13), U$10.46 (DVDD40), U$10.47 (DVDD41), U$10.48 (DVDD25)

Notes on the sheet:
CONFIG_P
CONFIG_N
VCC1V2
AVCC1V2
CLK1
REPORT_N
AVCC3V3
CONFIG_N1
CONFIG_P1
RST
REPORT_P
CLK
CONFIG_N10
CONFIG_P10
CLK2
CONFIG_N2
CONFIG_P2
CLK3
CONFIG_N3
CONFIG_P3
CLK4
CONFIG_N4
CONFIG_P4
CLK5
CONFIG_N5
CONFIG_P5
CLK6
CONFIG_N6
CONFIG_P6
CLK7
CONFIG_N7
CONFIG_P7
CLK8
CONFIG_N8
CONFIG_P8
CLK9
CONFIG_N9
CONFIG_P9
CLK10
CLK_IO1

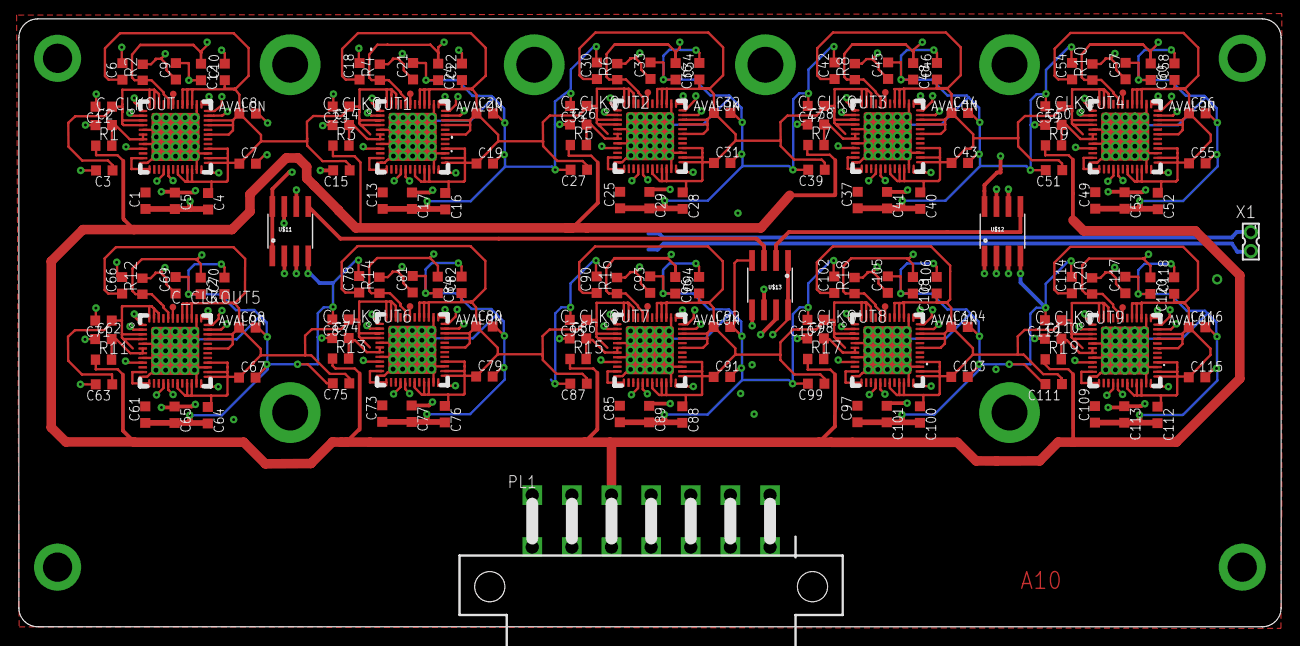
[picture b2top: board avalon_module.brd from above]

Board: 4 copper layers, 133.8 x 64.4 mm, 166 parts (1 on the bottom side), 64 nets.

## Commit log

2013-08-20 Initial directory structure.
2013-12-03 init version
2013-12-23 fixed clock settings
2013-12-24 added some datasheets, updated schematic

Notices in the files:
parts and their libraries:
SparkFun: Licensing: CC v3.0 Share-Alike You are welcome to use this library for commercial purposes.
